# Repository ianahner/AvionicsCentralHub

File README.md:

# Avionics Central Hub

## Design Goals
This project was designed to solve a number of problems encountered while laying out the electrical wiring for an experimental aircraft. I wanted to accomplish the following:
- Single Point Ground for all panel avionics
- Eliminate as many splices as possible from wiring harness
- Simplify harness design, ideally having only a single harness branch to each device
- Allow for easy future expansion or modification if an individual instrument is changed without having to rework significant portions of the harness

## Component Considerations
My panel consists of the following:
- GRT Horizon 10.1 PFD
- GRT Mini G2 MFD
- Garmin GNX375 GPS/XPDR
- Trig TX56A NavCom
- Small Switch and annunciator panel
- GRT Autopilot

## Physical Footprint
The GRT Horizon 10.1 EFIS includes mounting holes on the rear of the display unit for the GRT SafeFly GPS. As I am not using the SafeFly GPS in my build due to having the Garmin, I have made this board fit the mounting hole pattern of that device. This will allow the board to mount directly to the rear of the PFD. 

The board is slightly larger in outside dimensions than the SafeFly, but the mounting holes are the same. When mounting to the rear of the PFD this is no big deal, but if you are mounting in some other tucked away spot be aware of the outside dimensions. 

In the future I plan to design a simple 3D printed cover for this board. I'll add it to this repo if/when that ever happens.

## Audio Mixing Resistors
This audio mixing solution is of course not intended to be a high fidelity audio solution. The intention here is to mix the mono "annunciator" signals from instruments for messages like "AP Disconnect" or "Minimums." I highly discourage anyone from using this solution for something like radio audio or even non-essential music audio as the results are likely to be less than desirable. For the purposes of mixing alert tones, it should be perfectly acceptable.

The resistors exist simply to prevent one audio device from backfeeding the driver of another device. The value was chosen based on the output impedance of the devices I have, but should be reasonable for the vast majority of situations you're likely to encounter. 

As an aside, though this LOOKS extremely hacky (and it sort of is) it comes straight out of the manual for the PSE certified intercom and others, and is a rather common old-school approach to audio mixing, back before engineering was invented. 

## LED Series Resistor values assumptions
The LED series resistors R1-R5 are optional for use with panel mount LEDs that either don't have a series resistor, or have a voltage range that isn't high enough for the 14.5V our alternators tend to run. 

The resistor specified in the BOM below is a 620Ω which was calculated to provide 20mA to a 2V LED assuming a bus voltage of 14.5V. Adjust this to your needs, or simply install a 0Ω jumper. 

## Why does Fuse F1 exist? 
This fuse does not need to exist at all, and you can jumper it in many cases if you do not like the idea of a fuse in your ground. The purpose of that fuse is rather specific to my application. I intend to ground GND1 (J6) directly to battery negative in my aircraft. My aircraft is a composite pusher configuration with the battery in the nose and the engine on the rear. There is a single very large negative battery lead running the length of the fuselage, and the fuselage being composite is of no use for grounding. 

The intention in this application is to run the secondary fused ground all the way back to the grounding stud where the primary alternator is grounded. This protects against any failure of the main battery negative or of the GND1 connection to the battery. 

I have included the fuse to protect against a very unlikely fault condition where that main ground lead to the rear of the airplane is damaged, or the engine to firewall bonding strap is broken. In that case if a pilot were to attempt to start the aircraft, the starter current could try to go through this board. That would not only blow the traces off the board, but also potentially damage the relatively small #12 or #10 wire used for this redundant ground. 

The fuse should be sized to protect the wire, assumed to be 20-30A. If a ground strap is broken and a pilot tries to start the plane, the fuse will blow. The pilot will also be unable to start the plane, so this should be sign enough to troubleshoot the problem, and then replace the fuse. A fuse is fine here instead of a CB because there is no reasonable situation where this would blow in flight that could be fixed by resetting a CB. 

## BOM for Population
QTY | DK PN | REFs
--- | --- | ---
1 | 36-3568-ND | F1
1 | A35173-ND | J8
5 | A35183-ND | J1, J2, J3, J4, J5
1 | A35186-ND | J9
2 | 63824 | J6, J7
5 | 541-RCP1206W620RFEACT-ND | R1, R2, R3, R4, R5
3 | RMCF0805JT470RCT-ND | R6, R7, R8

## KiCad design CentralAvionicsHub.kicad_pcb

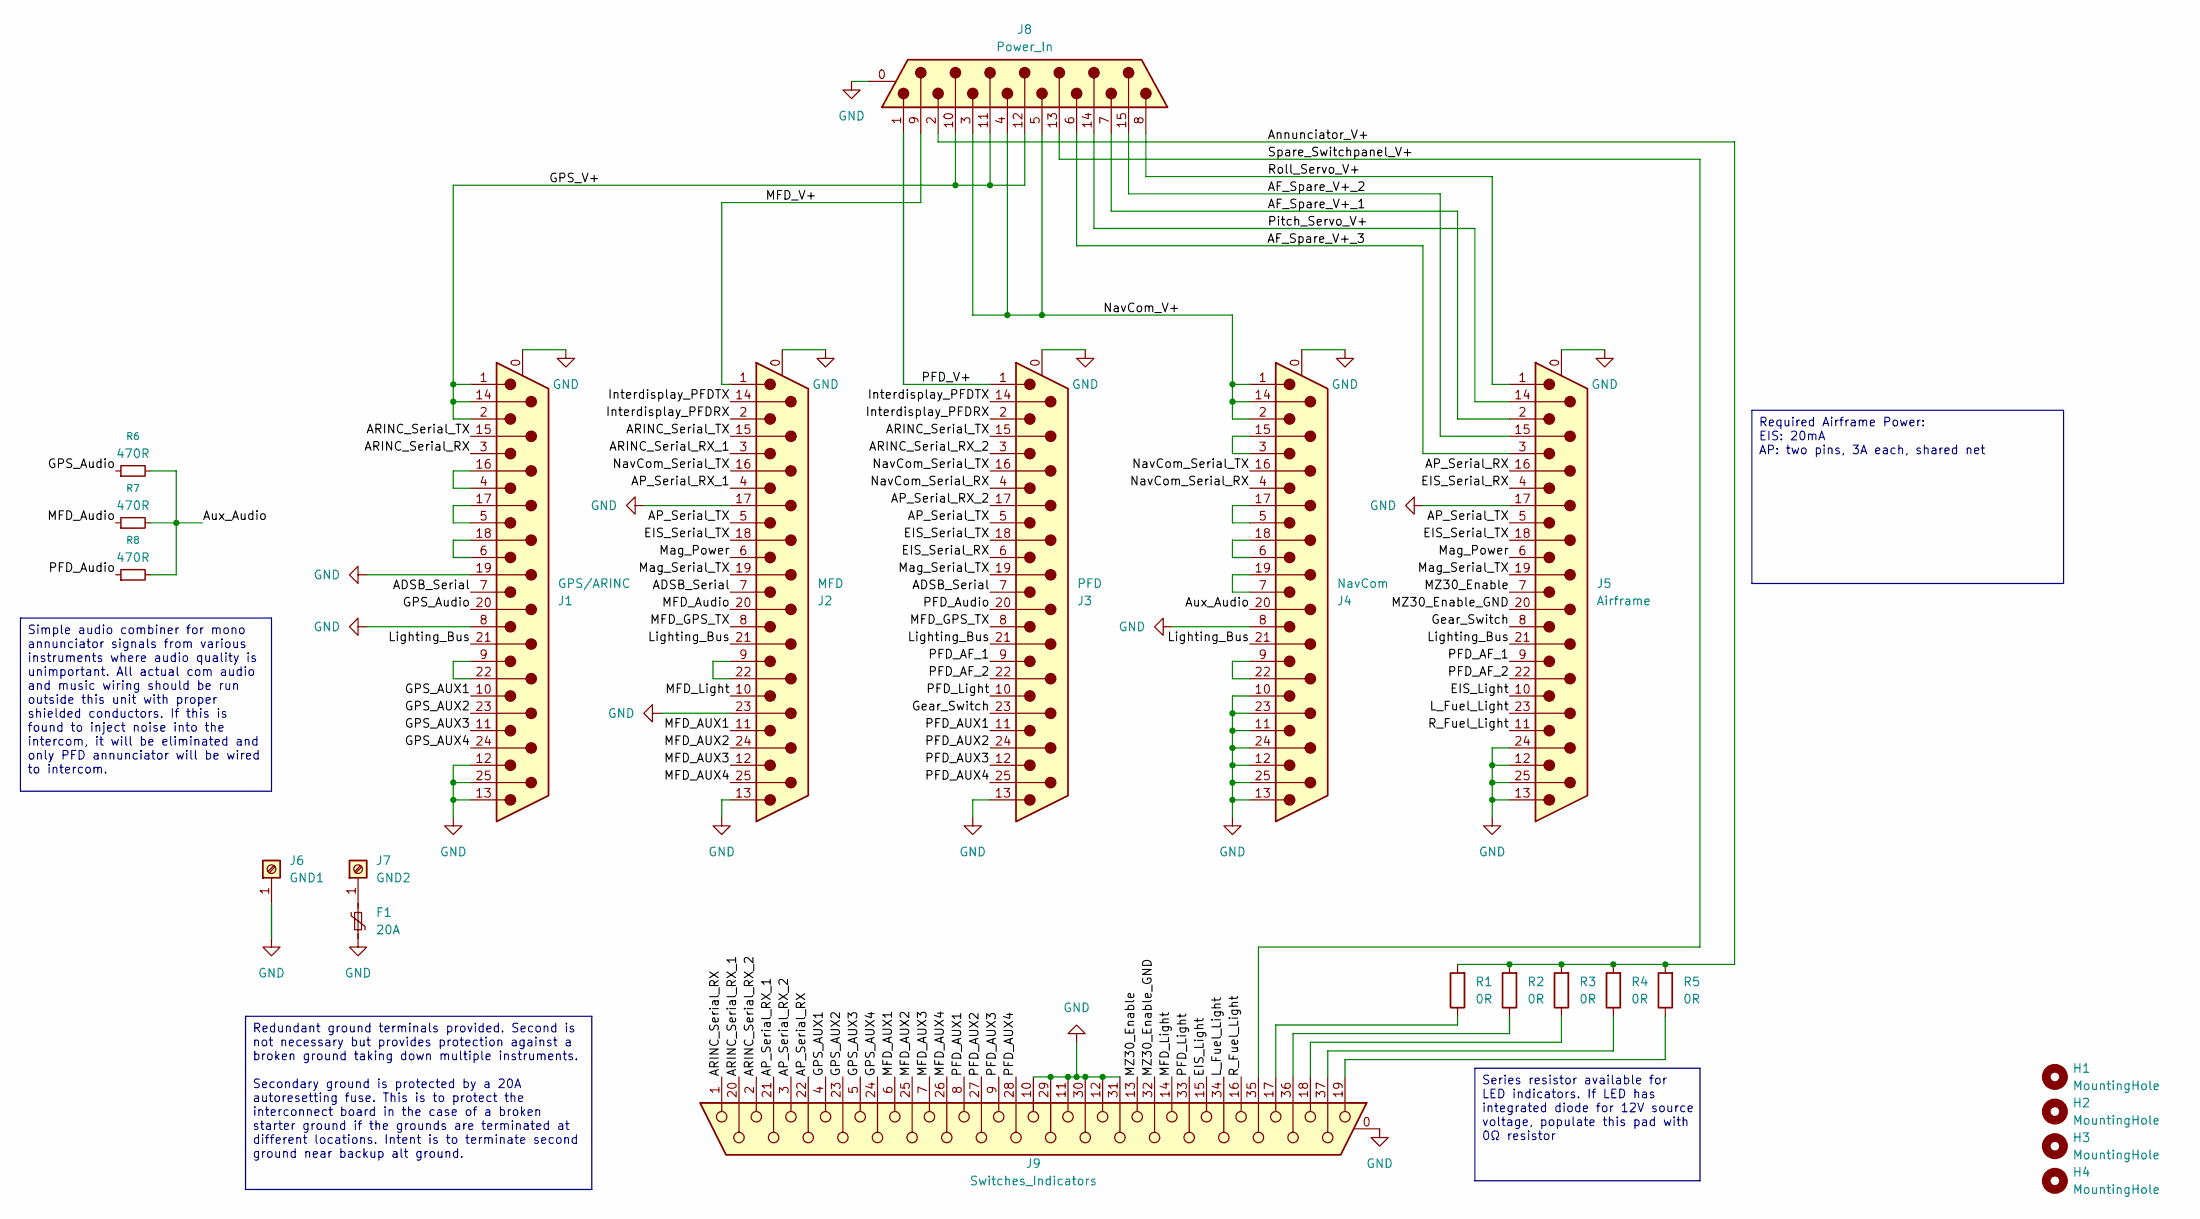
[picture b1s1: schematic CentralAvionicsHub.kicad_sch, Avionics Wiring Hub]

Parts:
F1: 20A; FUSE_3568
H1, H2, H3, H4: MountingHole; MountingHole_4.3mm_M4_ISO7380
J1: GPS/ARINC; DSUB-25_Socket_Vertical_P2.77x2.84mm_MountingHoles
J2: MFD; DSUB-25_Socket_Vertical_P2.77x2.84mm_MountingHoles
J3: PFD; DSUB-25_Socket_Vertical_P2.77x2.84mm_MountingHoles
J4: NavCom; DSUB-25_Socket_Vertical_P2.77x2.84mm_MountingHoles
J5: Airframe; DSUB-25_Socket_Vertical_P2.77x2.84mm_MountingHoles
J6: GND1; 63824
J7: GND2; 63824
J8: Power_In; 5787683 15 Pin Female Vertical
J9: Switches_Indicators; DSUB-37_Socket_Vertical_P2.77x2.84mm_MountingHoles
R1, R2, R3, R4, R5: 0R; R_1206_3216Metric_Pad1.30x1.75mm_HandSolder
R6, R7, R8: 470R; R_0805_2012Metric

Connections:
/ADSB_Serial: J1.7, J2.7, J3.7
/AF_Spare_V+_1: J5.2, J8.7
/AF_Spare_V+_2: J5.15, J8.15
/AF_Spare_V+_3: J5.3, J8.6
/AP_Serial_RX: J5.16, J9.22
/AP_Serial_RX_1: J2.4, J9.21
/AP_Serial_RX_2: J3.17, J9.3
/AP_Serial_TX: J2.5, J3.5, J5.5
/ARINC_Serial_RX: J1.3, J9.1
/ARINC_Serial_RX_1: J2.3, J9.20
/ARINC_Serial_RX_2: J3.3, J9.2
/ARINC_Serial_TX: J1.15, J2.15, J3.15
/Annunciator_V+: J8.2, R1.2, R2.2, R3.2, R4.2, R5.2
/Aux_Audio: J4.20, R6.2, R7.2, R8.2
/EIS_Light: J5.10, J9.15
/EIS_Serial_RX: J3.6, J5.4
/EIS_Serial_TX: J2.18, J3.18, J5.18
/GPS_AUX1: J1.10, J9.4
/GPS_AUX2: J1.23, J9.23
/GPS_AUX3: J1.11, J9.5
/GPS_AUX4: J1.24, J9.24
/GPS_Audio: J1.20, R6.1
/GPS_V+: J1.1, J1.2, J1.14, J8.10, J8.11 (P111), J8.12
/Gear_Switch: J3.23, J5.8
/Interdisplay_PFDRX: J2.2, J3.2
/Interdisplay_PFDTX: J2.14, J3.14
/L_Fuel_Light: J5.23, J9.34
/Lighting_Bus: J1.21, J2.21, J3.21, J4.21, J5.21
/MFD_AUX1: J2.11, J9.6
/MFD_AUX2: J2.24, J9.25
/MFD_AUX3: J2.12, J9.7
/MFD_AUX4: J2.25, J9.26
/MFD_Audio: J2.20, R7.1
/MFD_GPS_TX: J2.8, J3.8
/MFD_Light: J2.10, J9.14
/MFD_V+: J2.1, J8.9
/MZ30_Enable: J5.7, J9.13
/MZ30_Enable_GND: J5.20, J9.32
/Mag_Power: J2.6, J5.6
/Mag_Serial_TX: J2.19, J3.19, J5.19
/NavCom_Serial_RX: J3.4, J4.4
/NavCom_Serial_TX: J2.16, J3.16, J4.16
/NavCom_V+: J4.1, J4.2, J4.14, J8.3, J8.4, J8.5
/PFD_AF_1: J3.9, J5.9
/PFD_AF_2: J3.22, J5.22
/PFD_AUX1: J3.11, J9.8
/PFD_AUX2: J3.24, J9.27
/PFD_AUX3: J3.12, J9.9
/PFD_AUX4: J3.25, J9.28
/PFD_Audio: J3.20, R8.1
/PFD_Light: J3.10, J9.33
/PFD_V+: J3.1, J8.1
/Pitch_Servo_V+: J5.14, J8.14
/R_Fuel_Light: J5.11, J9.16
/Roll_Servo_V+: J5.1, J8.8
/Spare_Switchpanel_V+: J8.13, J9.35
GND: F1.2, J1.0 (PAD), J1.8, J1.12, J1.13, J1.19, J1.25, J2.0 (PAD), J2.13, J2.17, J2.23, J3.0 (PAD), J3.13, J4.0 (PAD), J4.8, J4.10, J4.11, J4.12, J4.13, J4.23, J4.24, J4.25, J5.0 (PAD), J5.12, J5.13, J5.17, J5.24, J5.25, J6.1, J8.0 (PAD), J9.0 (PAD), J9.10, J9.11, J9.12, J9.29, J9.30, J9.31
unnamed: J1.4, J1.16
unnamed: J1.5, J1.17
unnamed: J1.6, J1.18
unnamed: J1.9, J1.22
unnamed: J2.9, J2.22
unnamed: J4.3, J4.15
unnamed: J4.5, J4.17
unnamed: J4.6, J4.18
unnamed: J4.7, J4.19
unnamed: J4.9, J4.22
unnamed: F1.1, J7.1
unnamed: J9.17, R1.1
unnamed: J9.18, R3.1
unnamed: J9.19, R5.1
unnamed: J9.36, R2.1
unnamed: J9.37, R4.1

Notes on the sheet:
Simple audio combiner for mono annunciator signals from various instruments where audio quality is unimportant. All actual com audio and music wiring should be run outside this unit with proper shielded conductors. If this is found to inject noise into the intercom, it will be eliminated and only P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
Required Airframe Power: EIS: 20mA AP: two pins, 3A each, shared net
Redundant ground terminals provided. Second is not necessary but provides protection against a broken ground taking down multiple instruments. Secondary ground is protected by a 20A autoresetting fuse. This is to protect the interconnect board in the case of a broken starter ground if the grounds a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
Series resistor available for LED indicators. If LED has integrated diode for 12V source voltage, populate this pad with 0Ω resistor

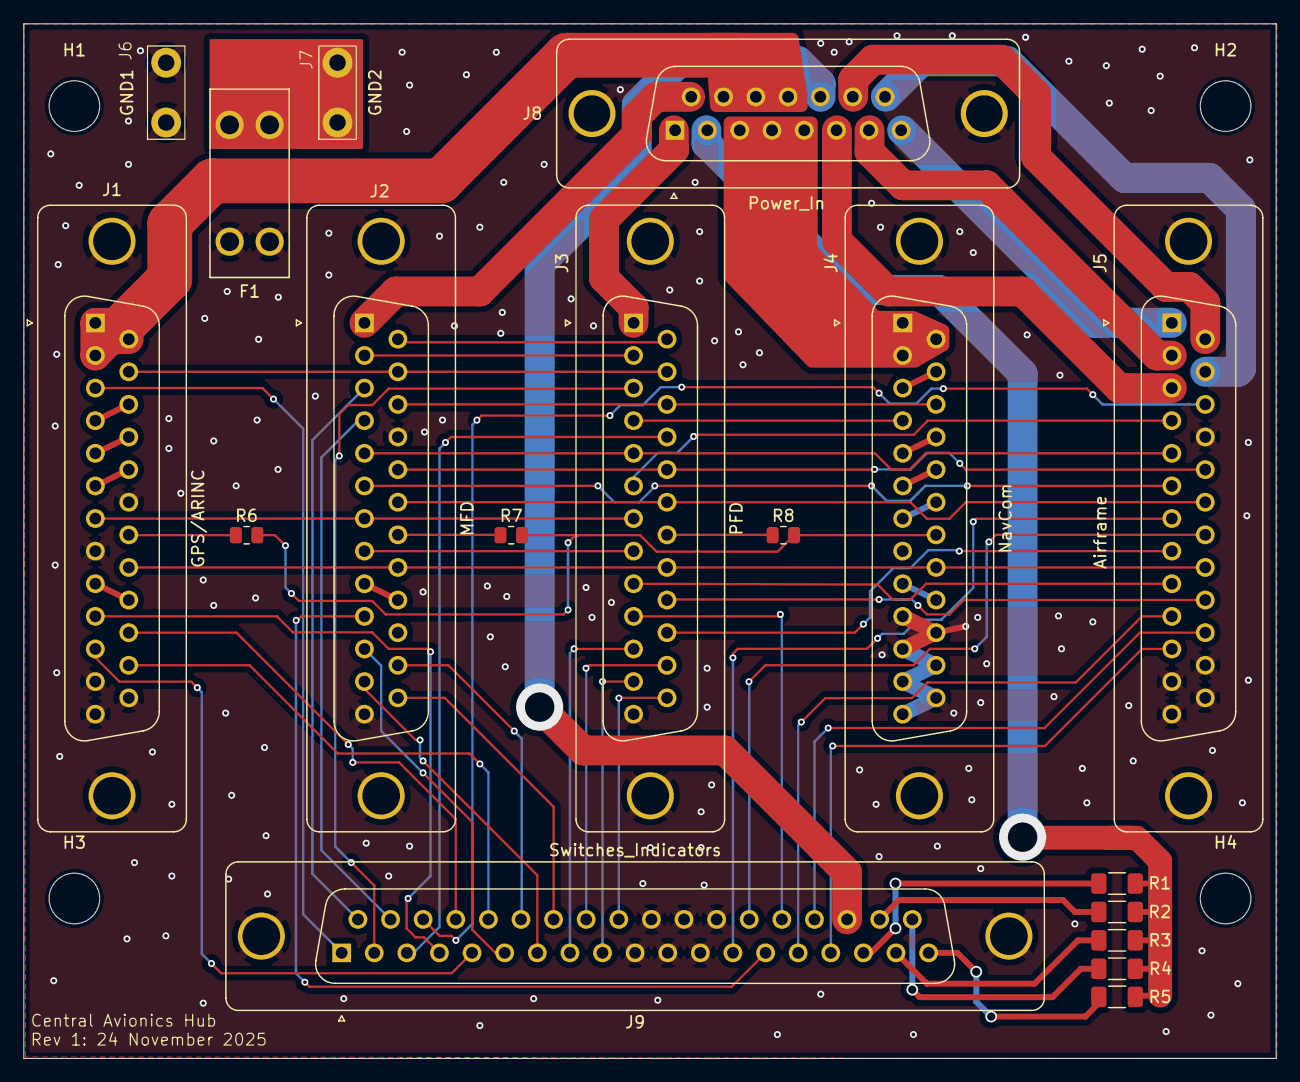
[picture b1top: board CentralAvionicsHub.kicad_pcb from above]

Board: 2 copper layers, 106.4 x 87.9 mm, 22 parts (0 on the bottom side), 73 nets.

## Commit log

2025-11-11 initial
2025-11-14 Schematic mostly finalized, preliminary board layout for basic space testing and sanity checking
2025-11-14 Basic layout commit
2025-11-17 Added mounting holes, aligned components, began power layout with properly sized traces.
2025-11-18 Power routing mostly complete. Rearranged pinout on power_in connector to support better routing. Broke a number of other traces in the process, will correct later.
2025-11-18 Removed Curved Traces
2025-11-18 Trace cleanup
2025-11-19 Refined layout. Still need to address gnd connector
2025-11-24 Minor Fixes, silkscreen updates.
2025-11-24 Changed Ground connections to 250 FASTON tabs. Updated silkscreen. Corrected minor DRC errors.
2025-11-24 Generated Gerbers
2025-11-24 Zipped Gerbers, Added 3D render
2025-11-25 Replaced F1 footprint with traditional fuseholder for Mini Blade Fuse.
    Changed R1-R5 to 1206
    Modified footprint of DA15 to match TE part
    Managed Libraries, regenerated gerbers at V1.
2025-11-25 Update README.md
    Readme Updates
2025-11-25 Update README.md
    More README updates
2025-12-19 Replot PDFs and 3d model
